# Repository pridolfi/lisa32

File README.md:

# LISA32

An ESP32 development board with both UART and JTAG interfaces.

## v0.1.0 prototype

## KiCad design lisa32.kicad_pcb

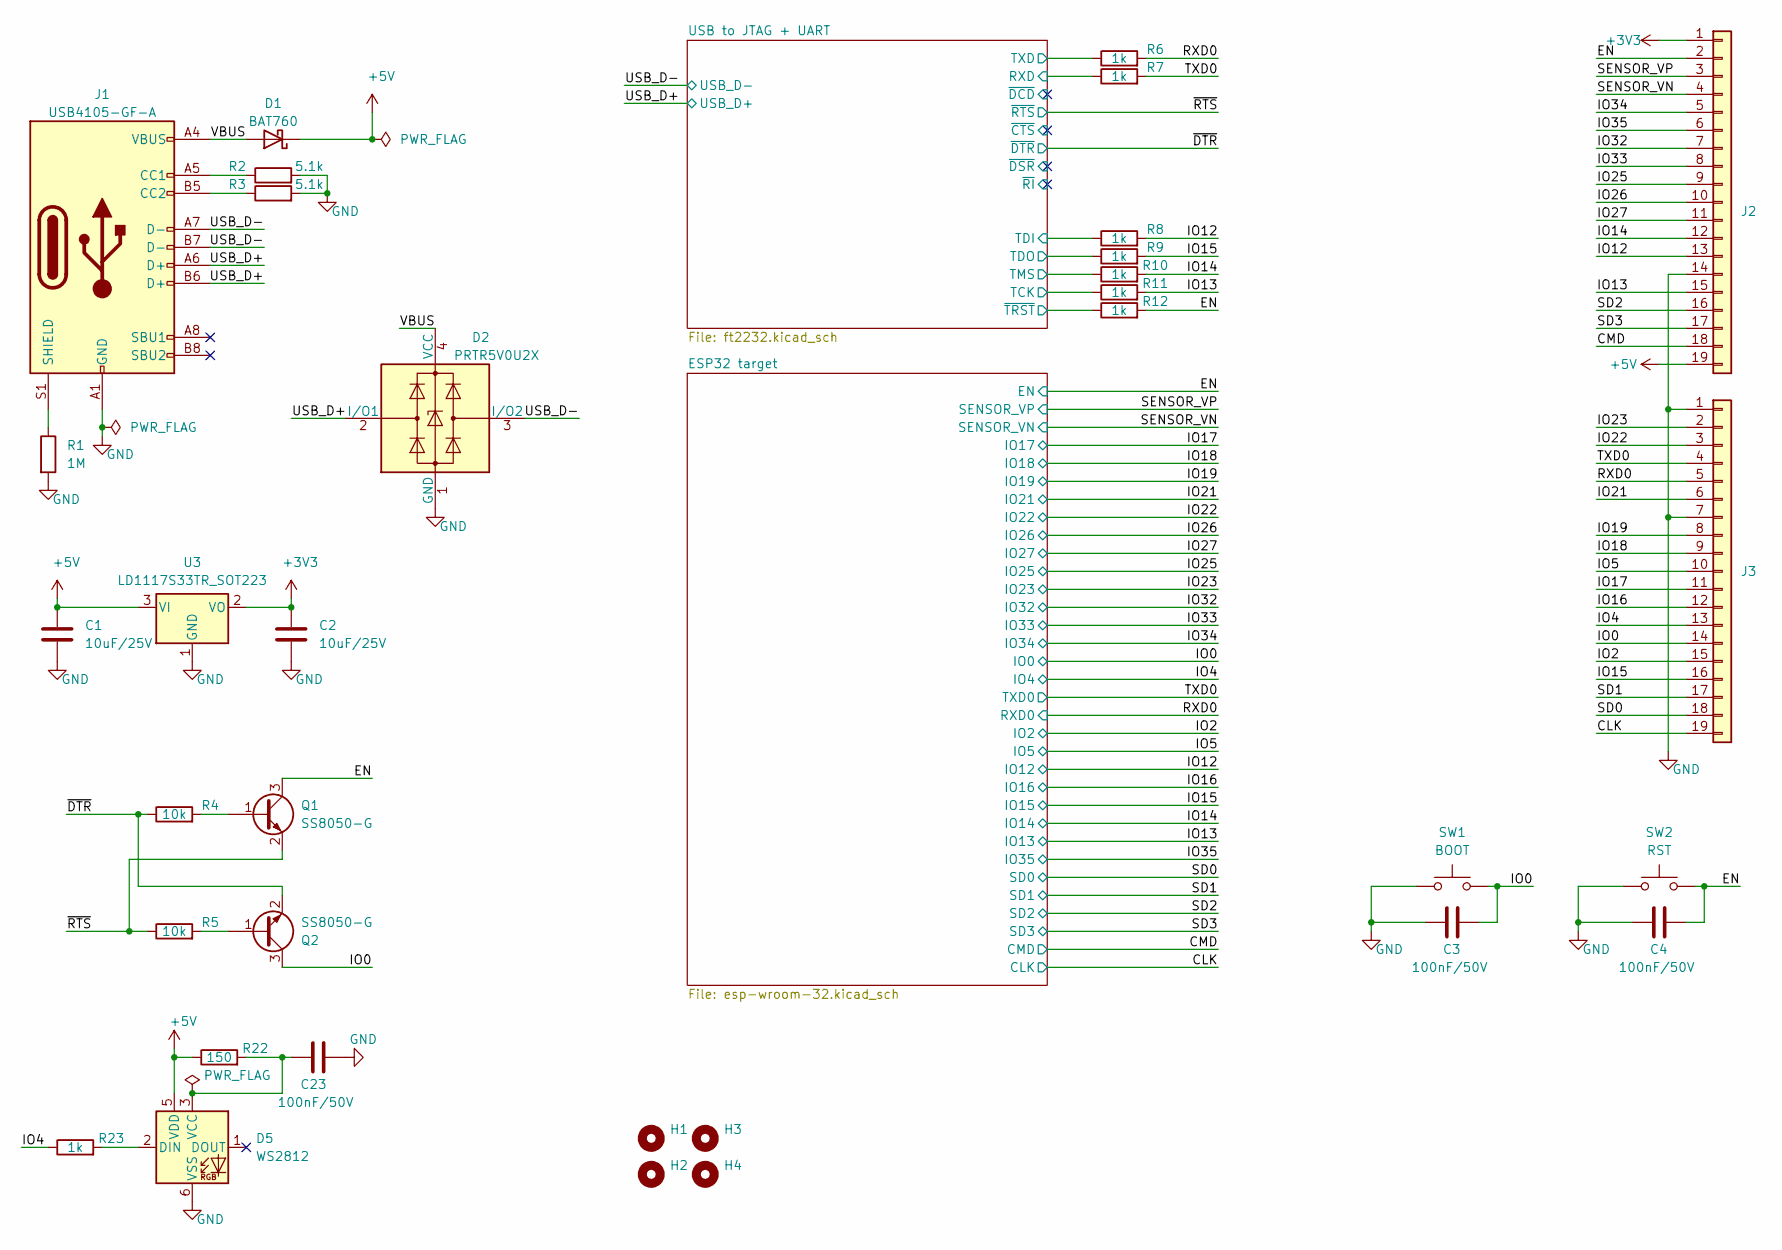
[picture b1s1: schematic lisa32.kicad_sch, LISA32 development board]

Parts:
C1, C2: 10uF/25V; C_1206_3216Metric
C3, C4, C23: 100nF/50V; C_0603_1608Metric
D1: BAT760; D_SOD-323
D2: PRTR5V0U2X; SOT-143
D5: WS2812; LED_WS2812_PLCC6_5.0x5.0mm_P1.6mm
H1, H2, H3, H4: MountingHole; MountingHole_2.2mm_M2
J1: USB4105-GF-A; USB_C_Receptacle_Palconn_UTC16-G
J2, J3: Conn_01x19; PinHeader_1x19_P2.54mm_Vertical
Q1, Q2: SS8050-G; SOT-23
R1: 1M; R_0603_1608Metric
R2, R3: 5.1k; R_0603_1608Metric
R4, R5: 10k; R_0603_1608Metric
R6, R7, R8, R9, R10, R11, R12, R23: 1k; R_0603_1608Metric
R22: 150; R_0603_1608Metric
SW1: BOOT; SW_SPST_B3U-1000P
SW2: RST; SW_SPST_B3U-1000P
U3: LD1117S33TR_SOT223; SOT-223-3_TabPin2

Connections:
+3V3: C2.1, J2.1, U3.2 (VO); also elsewhere on the board
+5V: C1.1, D1.1 (K), D5.5 (VDD), J2.19, R22.1, U3.3 (VI)
/CLK: J3.19; also elsewhere on the board
/CMD: J2.18; also elsewhere on the board
/EN: C4.2, J2.2, Q1.3 (C), R12.2, SW2.2; also elsewhere on the board
/IO0: C3.2, J3.14, Q2.3 (C), SW1.2; also elsewhere on the board
/IO2: J3.15; also elsewhere on the board
/IO4: J3.13, R23.1; also elsewhere on the board
/IO5: J3.10; also elsewhere on the board
/IO12: J2.13, R8.2; also elsewhere on the board
/IO13: J2.15, R11.2; also elsewhere on the board
/IO14: J2.12, R10.2; also elsewhere on the board
/IO15: J3.16, R9.2; also elsewhere on the board
/IO16: J3.12; also elsewhere on the board
/IO17: J3.11; also elsewhere on the board
/IO18: J3.9; also elsewhere on the board
/IO19: J3.8; also elsewhere on the board
/IO21: J3.6; also elsewhere on the board
/IO22: J3.3; also elsewhere on the board
/IO23: J3.2; also elsewhere on the board
/IO25: J2.9; also elsewhere on the board
/IO26: J2.10; also elsewhere on the board
/IO27: J2.11; also elsewhere on the board
/IO32: J2.7; also elsewhere on the board
/IO33: J2.8; also elsewhere on the board
/IO34: J2.5; also elsewhere on the board
/IO35: J2.6; also elsewhere on the board
/RXD: R7.1; also elsewhere on the board
/RXD0: J3.5, R6.2; also elsewhere on the board
/SD0: J3.18; also elsewhere on the board
/SD1: J3.17; also elsewhere on the board
/SD2: J2.16; also elsewhere on the board
/SD3: J2.17; also elsewhere on the board
/SENSOR_VN: J2.4; also elsewhere on the board
/SENSOR_VP: J2.3; also elsewhere on the board
/TCK: R11.1; also elsewhere on the board
/TDI: R8.1; also elsewhere on the board
/TDO: R9.1; also elsewhere on the board
/TMS: R10.1; also elsewhere on the board
/TXD: R6.1; also elsewhere on the board
/TXD0: J3.4, R7.2; also elsewhere on the board
/USB_D+: D2.2 (I/O1), J1.A6 (D+), J1.B6 (D+); also elsewhere on the board
/USB_D-: D2.3 (I/O2), J1.A7 (D-), J1.B7 (D-); also elsewhere on the board
/VBUS: D1.2 (A), D2.4 (VCC), J1.A4 (VBUS), J1.A9 (VBUS), J1.B4 (VBUS), J1.B9 (VBUS)
/~DTR: Q2.2 (E), R4.1; also elsewhere on the board
/~RTS: Q1.2 (E), R5.1; also elsewhere on the board
/~TRST: R12.1; also elsewhere on the board
GND: C1.2, C2.2, C3.1, C4.1, C23.2, D2.1 (GND), D5.6 (VSS), J1.A1 (GND), J1.A12 (GND), J1.B1 (GND), J1.B12 (GND), J2.14, J3.1, J3.7, R1.2, R2.2, R3.2, SW1.1, SW2.1, U3.1 (GND); also elsewhere on the board
unnamed: C23.1, D5.3 (VCC), R22.2
unnamed: D5.2 (DIN), R23.2
unnamed: J1.A5 (CC1), R2.1
unnamed: J1.B5 (CC2), R3.1
unnamed: J1.S1 (SHIELD), R1.1
unnamed: Q1.1 (B), R4.2
unnamed: Q2.1 (B), R5.2
no_connect_75: D5.1 (DOUT)
no_connect_76: J1.A8 (SBU1)
no_connect_77: J1.B8 (SBU2)

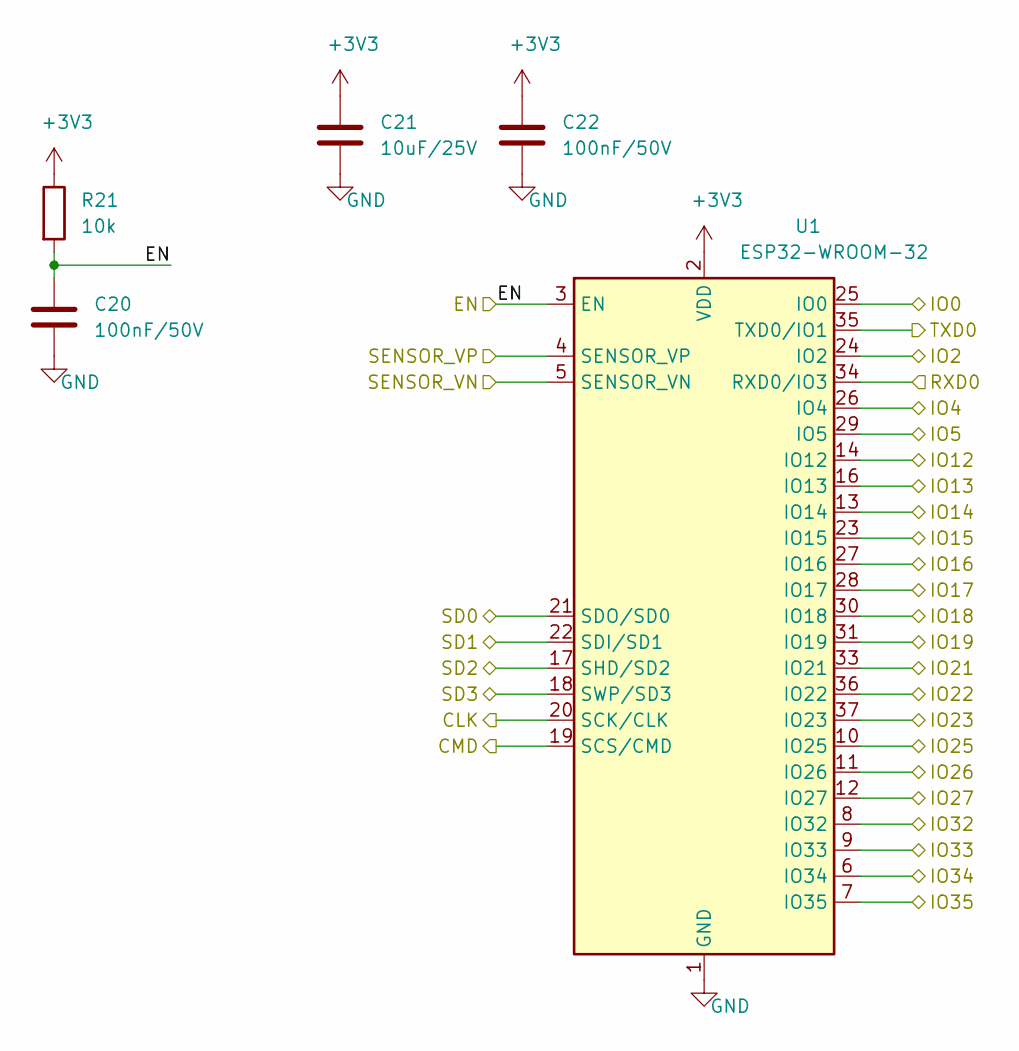
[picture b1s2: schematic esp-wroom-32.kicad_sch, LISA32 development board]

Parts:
C20, C22: 100nF/50V; C_0603_1608Metric
C21: 10uF/25V; C_1206_3216Metric
R21: 10k; R_0603_1608Metric
U1: ESP32-WROOM-32

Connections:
+3V3: C21.1, C22.1, R21.1, U1.2 (VDD); also elsewhere on the board
/CLK: U1.20 (SCK/CLK); also elsewhere on the board
/CMD: U1.19 (SCS/CMD); also elsewhere on the board
/EN: C20.1, R21.2, U1.3 (EN); also elsewhere on the board
/IO0: U1.25 (IO0); also elsewhere on the board
/IO2: U1.24 (IO2); also elsewhere on the board
/IO4: U1.26 (IO4); also elsewhere on the board
/IO5: U1.29 (IO5); also elsewhere on the board
/IO12: U1.14 (IO12); also elsewhere on the board
/IO13: U1.16 (IO13); also elsewhere on the board
/IO14: U1.13 (IO14); also elsewhere on the board
/IO15: U1.23 (IO15); also elsewhere on the board
/IO16: U1.27 (IO16); also elsewhere on the board
/IO17: U1.28 (IO17); also elsewhere on the board
/IO18: U1.30 (IO18); also elsewhere on the board
/IO19: U1.31 (IO19); also elsewhere on the board
/IO21: U1.33 (IO21); also elsewhere on the board
/IO22: U1.36 (IO22); also elsewhere on the board
/IO23: U1.37 (IO23); also elsewhere on the board
/IO25: U1.10 (IO25); also elsewhere on the board
/IO26: U1.11 (IO26); also elsewhere on the board
/IO27: U1.12 (IO27); also elsewhere on the board
/IO32: U1.8 (IO32); also elsewhere on the board
/IO33: U1.9 (IO33); also elsewhere on the board
/IO34: U1.6 (IO34); also elsewhere on the board
/IO35: U1.7 (IO35); also elsewhere on the board
/RXD0: U1.34 (RXD0/IO3); also elsewhere on the board
/SD0: U1.21 (SDO/SD0); also elsewhere on the board
/SD1: U1.22 (SDI/SD1); also elsewhere on the board
/SD2: U1.17 (SHD/SD2); also elsewhere on the board
/SD3: U1.18 (SWP/SD3); also elsewhere on the board
/SENSOR_VN: U1.5 (SENSOR_VN); also elsewhere on the board
/SENSOR_VP: U1.4 (SENSOR_VP); also elsewhere on the board
/TXD0: U1.35 (TXD0/IO1); also elsewhere on the board
GND: C20.2, C21.2, C22.2, U1.1 (GND), U1.15 (GND), U1.38 (GND), U1.39 (GND); also elsewhere on the board

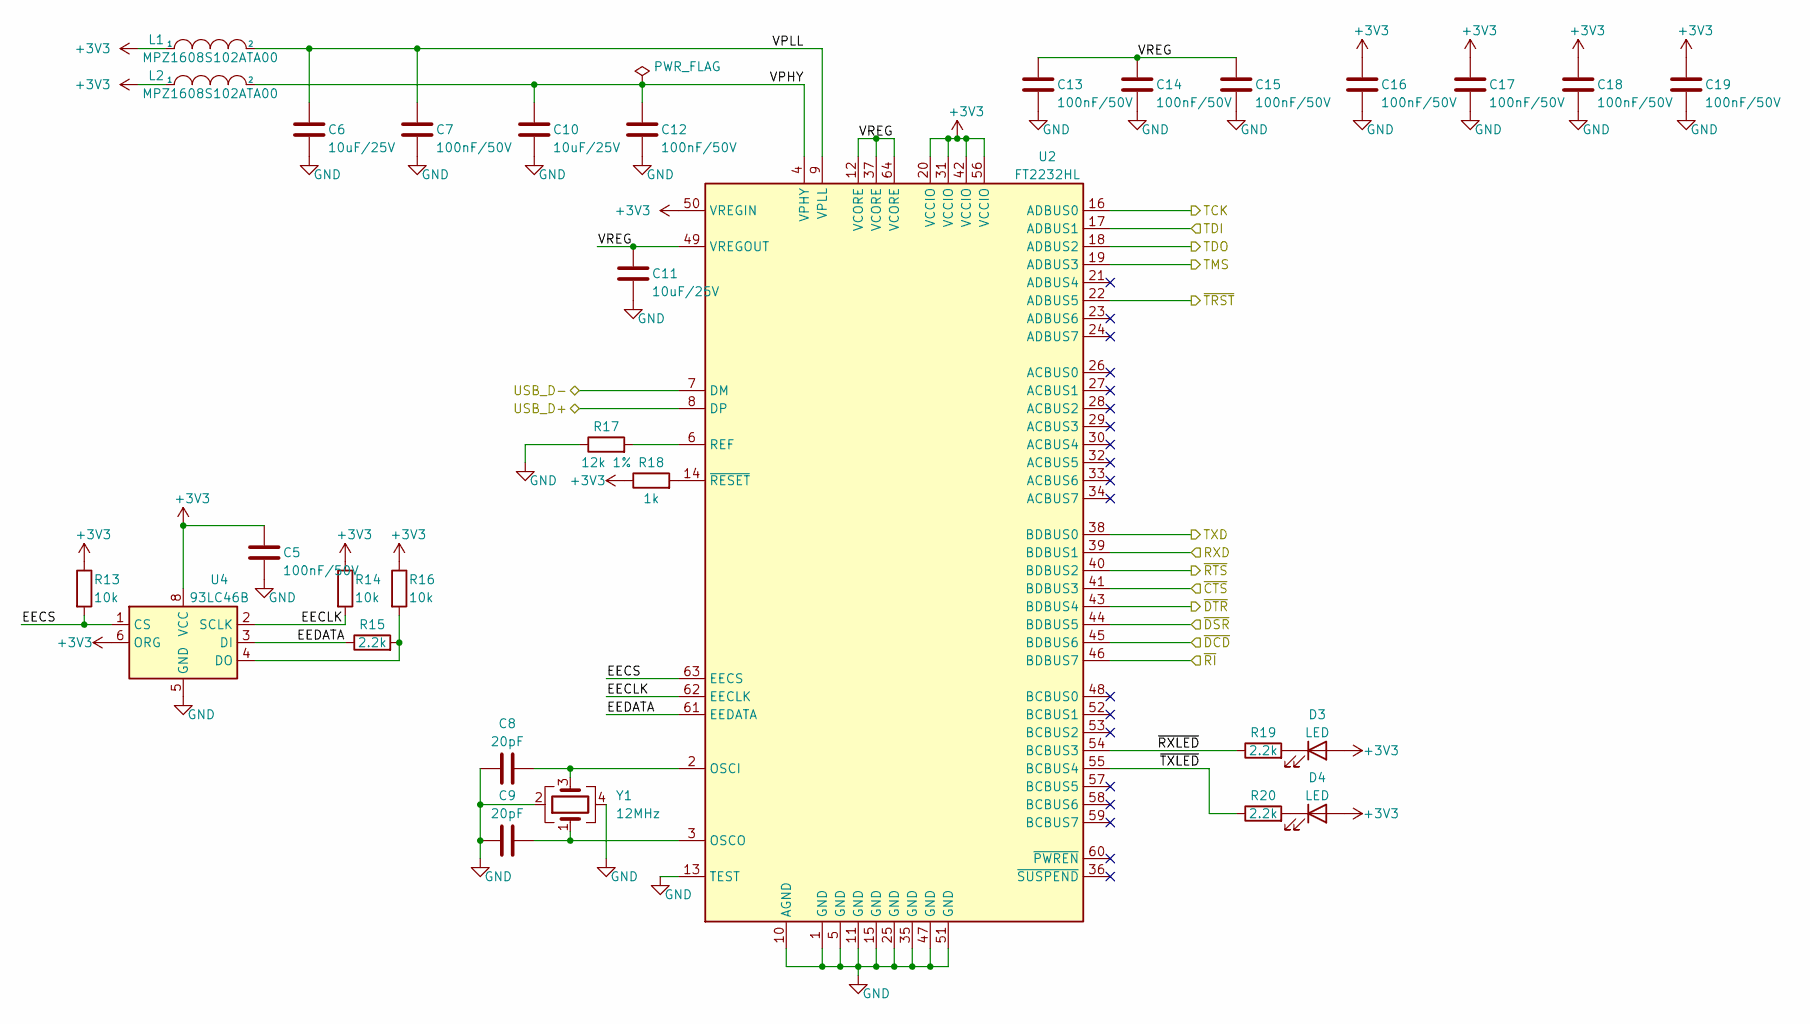
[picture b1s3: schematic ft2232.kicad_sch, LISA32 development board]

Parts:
C5, C7, C12, C13, C14, C15, C16, C17, C18, C19: 100nF/50V; C_0603_1608Metric
C6, C10, C11: 10uF/25V; C_1206_3216Metric
C8, C9: 20pF; C_0603_1608Metric
D3, D4: LED; LED_0603_1608Metric
L1, L2: MPZ1608S102ATA00; L_0603_1608Metric
R13, R14, R16: 10k; R_0603_1608Metric
R15, R19, R20: 2.2k; R_0603_1608Metric
R17: 12k 1%; R_0603_1608Metric
R18: 1k; R_0603_1608Metric
U2: FT2232HL; LQFP-64_10x10mm_P0.5mm
U4: 93LC46B; SO-8_3.9x4.9mm_P1.27mm
Y1: 12MHz; Crystal_SMD_3225-4Pin_3.2x2.5mm

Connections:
+3V3: C5.1, C16.1, C17.1, C18.1, C19.1, D3.2 (A), D4.2 (A), L1.1, L2.1, R13.1, R14.1, R16.1, R18.1, U2.20 (VCCIO), U2.31 (VCCIO), U2.42 (VCCIO), U2.50 (VREGIN), U2.56 (VCCIO), U4.6 (ORG), U4.8 (VCC); also elsewhere on the board
/RXD: U2.39 (BDBUS1); also elsewhere on the board
/TCK: U2.16 (ADBUS0); also elsewhere on the board
/TDI: U2.17 (ADBUS1); also elsewhere on the board
/TDO: U2.18 (ADBUS2); also elsewhere on the board
/TMS: U2.19 (ADBUS3); also elsewhere on the board
/TXD: U2.38 (BDBUS0); also elsewhere on the board
/USB to JTAG + UART/EECLK: R14.2, U2.62 (EECLK), U4.2 (SCLK)
/USB to JTAG + UART/EECS: R13.2, U2.63 (EECS), U4.1 (CS)
/USB to JTAG + UART/EEDATA: R15.1, U2.61 (EEDATA), U4.3 (DI)
/USB to JTAG + UART/VPHY: C10.1, C12.1, L2.2, U2.4 (VPHY)
/USB to JTAG + UART/VPLL: C6.1, C7.1, L1.2, U2.9 (VPLL)
/USB to JTAG + UART/VREG: C11.1, C13.1, C14.1, C15.1, U2.12 (VCORE), U2.37 (VCORE), U2.49 (VREGOUT), U2.64 (VCORE)
/USB to JTAG + UART/~RXLED: R19.1, U2.54 (BCBUS3)
/USB to JTAG + UART/~TXLED: R20.1, U2.55 (BCBUS4)
/USB_D+: U2.8 (DP); also elsewhere on the board
/USB_D-: U2.7 (DM); also elsewhere on the board
/~CTS: U2.41 (BDBUS3)
/~DCD: U2.45 (BDBUS6)
/~DSR: U2.44 (BDBUS5)
/~DTR: U2.43 (BDBUS4); also elsewhere on the board
/~RI: U2.46 (BDBUS7)
/~RTS: U2.40 (BDBUS2); also elsewhere on the board
/~TRST: U2.22 (ADBUS5); also elsewhere on the board
GND: C5.2, C6.2, C7.2, C8.1, C9.1, C10.2, C11.2, C12.2, C13.2, C14.2, C15.2, C16.2, C17.2, C18.2, C19.2, R17.1, U2.1 (GND), U2.5 (GND), U2.10 (AGND), U2.11 (GND), U2.13 (TEST), U2.15 (GND), U2.25 (GND), U2.35 (GND), U2.47 (GND), U2.51 (GND), U4.5 (GND), Y1.2, Y1.4; also elsewhere on the board
unnamed: C8.2, U2.2 (OSCI), Y1.3
unnamed: C9.2, U2.3 (OSCO), Y1.1
unnamed: D3.1 (K), R19.2
unnamed: D4.1 (K), R20.2
unnamed: R15.2, R16.2, U4.4 (DO)
unnamed: R17.2, U2.6 (REF)
unnamed: R18.2, U2.14 (~RESET)
no_connect_78: U2.21 (ADBUS4)
no_connect_79: U2.23 (ADBUS6)
no_connect_80: U2.24 (ADBUS7)
no_connect_81: U2.26 (ACBUS0)
no_connect_82: U2.27 (ACBUS1)
no_connect_83: U2.28 (ACBUS2)
no_connect_84: U2.29 (ACBUS3)
no_connect_85: U2.30 (ACBUS4)
no_connect_86: U2.32 (ACBUS5)
no_connect_87: U2.33 (ACBUS6)
no_connect_88: U2.34 (ACBUS7)
no_connect_89: U2.36 (~SUSPEND)
no_connect_90: U2.48 (BCBUS0)
no_connect_91: U2.52 (BCBUS1)
no_connect_92: U2.53 (BCBUS2)
no_connect_93: U2.57 (BCBUS5)
no_connect_94: U2.58 (BCBUS6)
no_connect_95: U2.59 (BCBUS7)
no_connect_96: U2.60 (~PWREN)

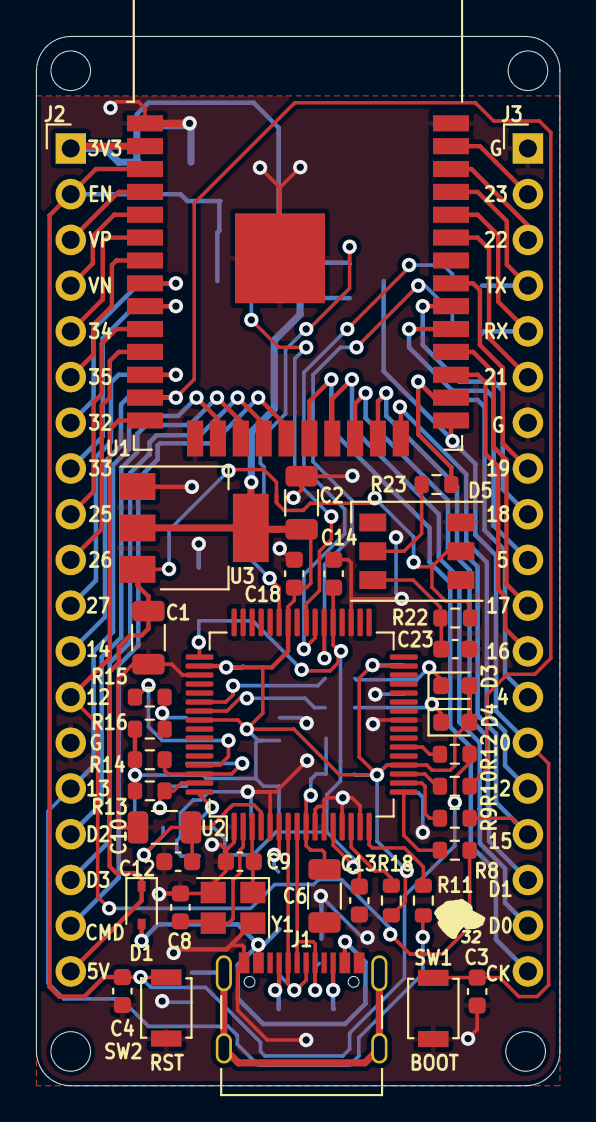
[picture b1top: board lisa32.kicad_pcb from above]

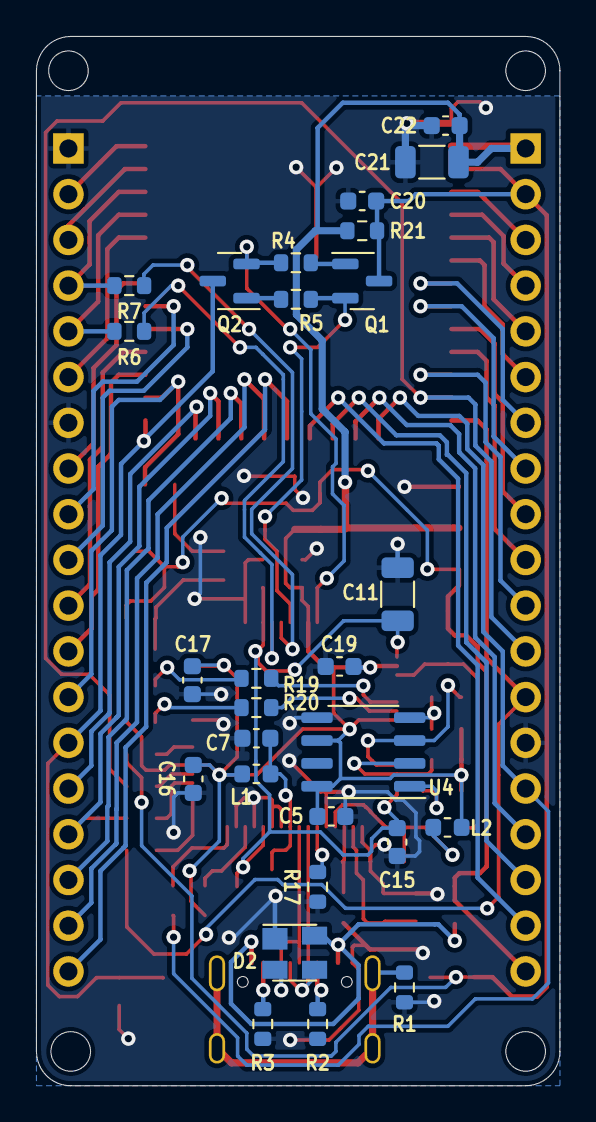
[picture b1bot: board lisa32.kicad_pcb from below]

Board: 2 copper layers, 29.1 x 58.3 mm, 69 parts (27 on the bottom side), 70 nets.

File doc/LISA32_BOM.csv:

Item,Qty,Reference(s),Value,PN,DK 07/01/2021
1,6,"C1, C2, C6, C10, C11, C21",10uF/25V,CL31A106KAHNNNE,‎1276-1075-1-ND‎
2,15,"C3, C4, C5, C7, C12, C13, C14, C15, C16, C17, C18, C19, C20, C22, C23",100nF/50V,CL10B104KB8NFNC,‎1276-1934-1-ND‎
3,2,"C8, C9",20pF,06035A200JAT2A,‎478-7912-1-ND‎
4,1,D1,BAT760,PMEG3020EJ,1727-3874-1-ND‎
5,1,D2,PRTR5V0U2X,"PRTR5V0U2X,215",‎1727-3884-1-ND‎
6,2,"D3, D4",LED,598-8070-107F,‎350-2035-1-ND‎
7,1,D5,WS2812,COM-11821,‎1568-1800-ND‎
8,1,J1,USB4105-GF-A,USB4105-GF-A,2073-USB4105-GF-ACT-ND‎
9,2,"L1, L2",MPZ1608S102ATA00,MPZ1608S102ATA00,‎445-8694-1-ND‎
10,2,"Q1, Q2",SS8050-G,SS8050-G,641-1790-1-ND‎
11,1,R1,1M,CRGCQ0603J1M0,‎A130109CT-ND‎
12,2,"R2, R3",5.1k,CRCW06035K10FKEBC,‎541-CRCW06035K10FKEBCCT-ND‎
13,6,"R4, R5, R13, R14, R16, R21",10k,CRCW060310K0FKEBC,541-CRCW060310K0FKEBCCT-ND‎
14,9,"R6, R7, R8, R9, R10, R11, R12, R18, R23",1k,RMCF0603FT1K00,‎RMCF0603FT1K00CT-ND‎
15,3,"R15, R19, R20",2.2k,CRCW06032K20FKEB,‎541-CRCW06032K20FKEBCT-ND‎
16,1,R17,12k 1%,RMCF0603FT12K0,‎RMCF0603FT12K0CT-ND‎
17,1,R22,150,RMCF0603FT150R,‎RMCF0603FT150RCT-ND‎
18,2,"SW1, SW2",BOOT/RST,B3U-1000P,‎SW1020CT-ND‎
19,1,U1,ESP32-WROOM-32,ESP32-WROOM-32E,‎1965-ESP32-WROOM-32E(4MB)CT-ND‎
20,1,U2,FT2232HL,FT2232HL-REEL,768-1024-1-ND‎
21,1,U3,LD1117S33TR_SOT223,LD1117S33TR,‎497-1242-1-ND‎
22,1,U4,93LC46B,93LC46B,93LC46BT-I/SNCT-ND‎
23,1,Y1,12MHz,403C11A12M00000,‎CTX1430CT-ND‎

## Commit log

2020-12-31 sch wip
2020-12-31 erc ok
2020-12-31 wip footprint assoc
2021-01-01 placing test
2021-01-02 fix autoprogram signals
2021-01-02 sch update
2021-01-03 wip placing
2021-01-06 routing completed
2021-01-07 v0.1.0
2021-01-07 add PN
2021-01-30 readme and button labels
2021-02-01 v0.1.1
2021-02-01 udpate bom and sch
